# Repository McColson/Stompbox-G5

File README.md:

# Stompbox-G5
Guitar preamp stompbox

<br />Ce(tte) œuvre est mise à disposition selon les termes de la <a rel="license" href="http://creativecommons.org/licenses/by-nc-sa/4.0/">Licence Creative Commons Attribution - Pas d’Utilisation Commerciale - Partage dans les Mêmes Conditions 4.0 International</a>.

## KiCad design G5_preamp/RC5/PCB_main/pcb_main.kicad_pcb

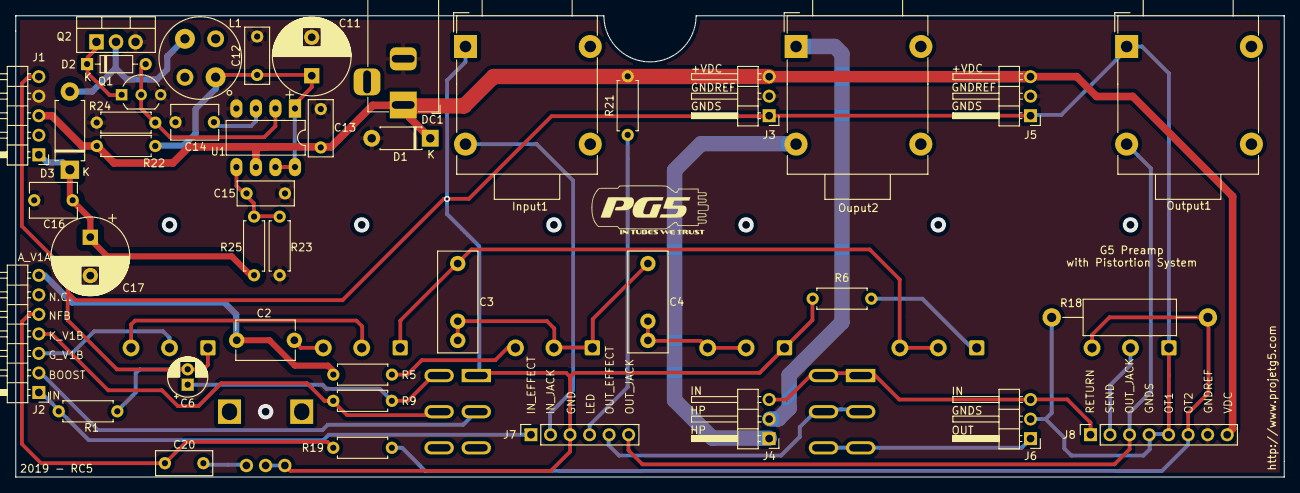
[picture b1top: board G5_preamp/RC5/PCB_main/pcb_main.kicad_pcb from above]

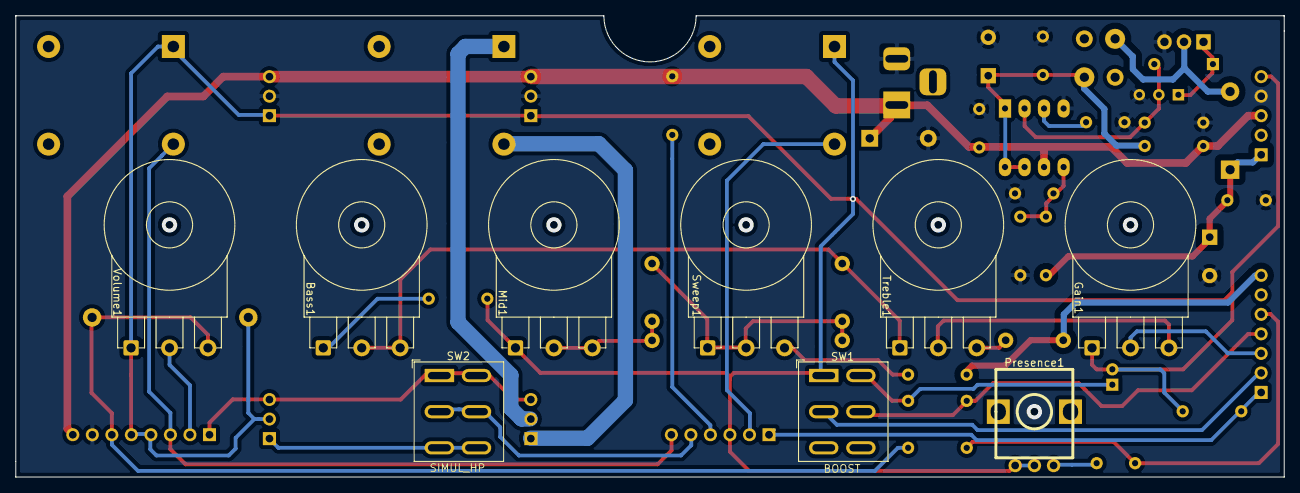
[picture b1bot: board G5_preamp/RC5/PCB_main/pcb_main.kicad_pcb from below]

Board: 2 copper layers, 165.0 x 60.0 mm, 52 parts (9 on the bottom side), 35 nets.

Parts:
Bass1: 250k log; Potentiometer_Alpha_RV16AF41_Single_Vertical
C2: 250pF; C_Disc_D7.5mm_W5.0mm_P7.50mm
C3: 100nF; C_Rect_L13.0mm_W5.0mm_P7.5mm_or_P10.00mm_FKS3_FKP3_MKS4
C4: 47nF; C_Rect_L13.0mm_W5.0mm_P7.5mm_or_P10.00mm_FKS3_FKP3_MKS4
C6: 22µF/25V; CP_Radial_D5.0mm_P2.00mm
C11: 470µ; CP_Radial_D10.0mm_P5.00mm
C12, C13, C15: 100nf; C_Rect_L7.2mm_W3.0mm_P5.00mm_FKS2_FKP2_MKS2_MKP2
C14: 470p; C_Disc_D6.0mm_W4.4mm_P5.00mm
C16: 10n/400V; C_Disc_D6.0mm_W4.4mm_P5.00mm
C17: 4.7µ/400V; CP_Radial_D10.0mm_P5.00mm
C20: 470nf; C_Rect_L7.2mm_W3.0mm_P5.00mm_FKS2_FKP2_MKS2_MKP2
D1: 1N4007; D_DO-41_SOD81_P7.62mm_Horizontal
D2: 1N4148; D_DO-35_SOD27_P7.62mm_Horizontal
D3: BYV26; D_DO-15_P10.16mm_Horizontal
DC1: Barrel_Jack; BarrelJack_Horizontal
Gain1: 1M log; Potentiometer_Alpha_RV16AF41_Single_Vertical
Input1: Input; Jack_6.35mm_Neutrik_NMJ4HCD2_Horizontal
J1: PSU_TUBE; PinHeader_1x05_P2.54mm_Horizontal
J2: PCB_TUBE; PinHeader_1x07_P2.54mm_Horizontal
J3: PSU_AMP; PinHeader_1x03_P2.54mm_Horizontal
J4: AMP; PinHeader_1x03_P2.54mm_Horizontal
J5: PSU_SIMCAB; PinHeader_1x03_P2.54mm_Horizontal
J6: SIMCAB; PinHeader_1x03_P2.54mm_Horizontal
J7: 3PDT; PinSocket_1x06_P2.54mm_Vertical
J8: PCB_OUTPUT; PinSocket_1x08_P2.54mm_Vertical
L1: 220µH/1.5A; L_Radial_D10.5mm_P5.00mm_MuRATA_1200RS
Mid1: 100k log; Potentiometer_Alpha_RV16AF41_Single_Vertical
Ouput2: HP; Jack_6.35mm_Neutrik_NMJ4HCD2_Horizontal
Output1: Output; Jack_6.35mm_Neutrik_NMJ4HCD2_Horizontal
Presence1: 50k lin; RV09AF-40-ALPHA-POT
Q1: MPS751; TO-92_Inline_Wide
Q2: IRF740; TO-220-3_Vertical
R1: 1M; R_Axial_DIN0207_L6.3mm_D2.5mm_P7.62mm_Horizontal
R5: 47k; R_Axial_DIN0207_L6.3mm_D2.5mm_P7.62mm_Horizontal
R6: 15k; R_Axial_DIN0207_L6.3mm_D2.5mm_P7.62mm_Horizontal
R9, R21: 100k; R_Axial_DIN0207_L6.3mm_D2.5mm_P7.62mm_Horizontal
R18: 68R/2W; R_Axial_DIN0414_L11.9mm_D4.5mm_P20.32mm_Horizontal
R19: 1.5k; R_Axial_DIN0207_L6.3mm_D2.5mm_P7.62mm_Horizontal
R22: 0.22R; R_Axial_DIN0207_L6.3mm_D2.5mm_P7.62mm_Horizontal
R23: 1.8k; R_Axial_DIN0207_L6.3mm_D2.5mm_P7.62mm_Horizontal
R24: 1k; R_Axial_DIN0207_L6.3mm_D2.5mm_P7.62mm_Horizontal
R25: 430k; R_Axial_DIN0207_L6.3mm_D2.5mm_P7.62mm_Horizontal
SW1: Boost; SW_CK_Lever_DPDT_72xx
SW2: SIMCAB; SW_CK_Lever_DPDT_72xx
Sweep1: 50k lin; Potentiometer_Alpha_RV16AF41_Single_Vertical
Treble1: 250k lin; Potentiometer_Alpha_RV16AF41_Single_Vertical
U1: MC34063AP; DIP-8_W7.62mm_LongPads
U2: PG5_Logo; PG5_Logo_15mm_SilkScreen
Volume1: 1k; Potentiometer_Alpha_RV16AF41_Single_Vertical

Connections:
/A_V1A: C2.2, J2.7, R5.1
/BOOST: J2.2, SW1.2
/G_V1B: Gain1.2, J2.3
/HP1: J4.1, Ouput2.T
/HP2: J4.2, Ouput2.S
/HT1: D3.2, L1.2, Q2.2
/HT2: C16.1, C17.1, D3.1, J1.1, R25.1
/IN_EFFECT: J2.1, J7.1, R1.1
/IN_JACK: Input1.T, J7.2
/K_V1B: J2.4, R9.1, SW1.5
/LED: J7.4, R21.1
/NFB: C20.2, J2.5, R19.1
/OT2: J8.6, R18.1, R19.2, Volume1.3
/OUT_EFFECT: J7.5, SW2.2, SW2.5
/OUT_JACK: J7.6, J8.3, Output1.T
/PEAK: C11.1, C12.1, L1.1, R22.2, U1.1, U1.7, U1.8
/RETURN: J4.3, J6.3, J8.1, SW2.1, SW2.4
/SEND: J8.2, Volume1.2
/SIMCAB_OUT: J6.1, SW2.3, SW2.6
/VDC: C13.1, D1.1, DC1.1, J1.3, J3.3, J5.3, J8.8, R21.2, R22.1, U1.6
GNDREF: C11.2, C12.2, C13.2, C14.2, C15.2, C16.2, C17.2, D1.2, DC1.2, J1.4, J3.2, J5.2, J8.7, Q1.3, Q2.3, R23.2, R24.2, U1.4
GNDS: C6.2, Gain1.1, Input1.S, J1.5, J3.1, J5.1, J6.2, J7.3, J8.4, J8.5, Mid1.1, Output1.S, Presence1.1, Presence1.2, R1.2, R6.2, R18.2, SW1.1, Volume1.1
unnamed: Bass1.1, R6.1
unnamed: Bass1.2, Bass1.3, C3.1, Treble1.1
unnamed: C2.1, Treble1.3
unnamed: C3.2, C4.1, Sweep1.1, Sweep1.2
unnamed: C4.2, Mid1.2, Mid1.3
unnamed: C6.1, R9.2, SW1.4
unnamed: C14.1, U1.3
unnamed: C15.1, R23.1, R25.2, U1.5
unnamed: C20.1, Presence1.3
unnamed: D2.1, Q1.1, Q2.1
unnamed: D2.2, Q1.2, R24.1, U1.2
unnamed: Gain1.3, Treble1.2
unnamed: R5.2, Sweep1.3

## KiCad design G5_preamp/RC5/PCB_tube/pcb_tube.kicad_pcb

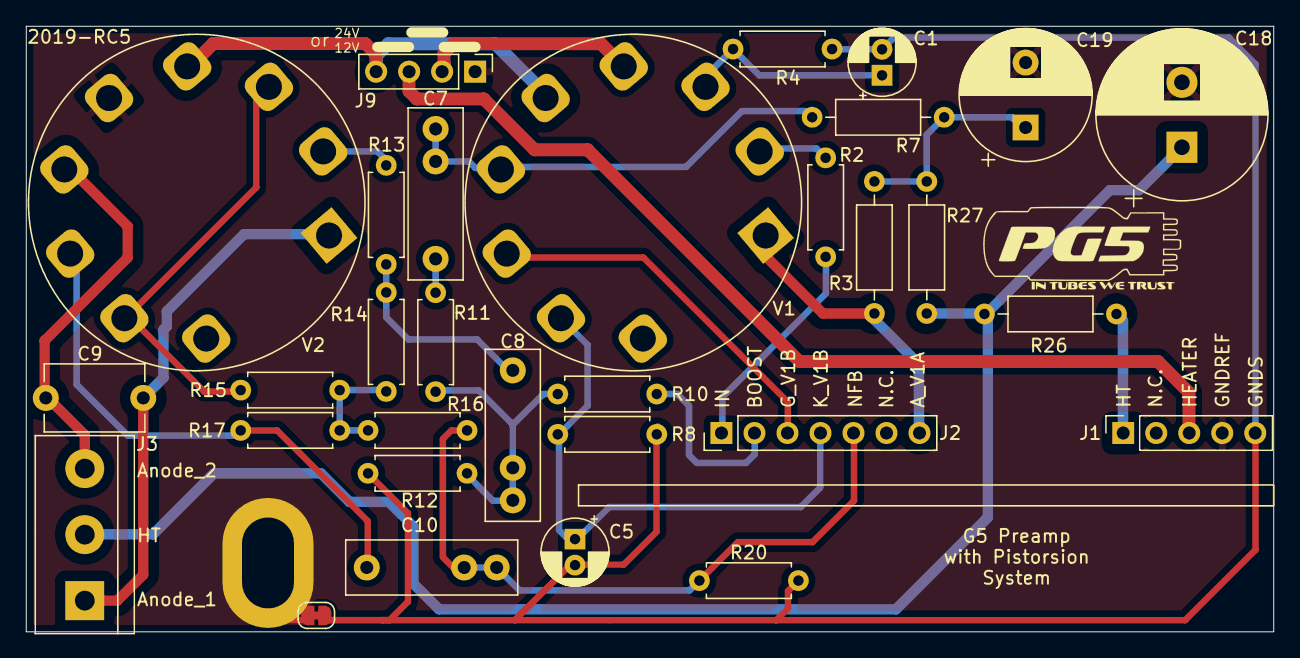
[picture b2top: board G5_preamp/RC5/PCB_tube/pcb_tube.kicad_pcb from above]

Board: 2 copper layers, 96.0 x 46.6 mm, 33 parts (0 on the bottom side), 26 nets.

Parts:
C1: 22µF/25v; CP_Radial_D5.0mm_P2.00mm
C5: 1µF/50v; CP_Radial_D5.0mm_P2.00mm
C7, C8: 22nF; C_Rect_L13.0mm_W4.0mm_P7.5mm_or_P10.00mm_MKS4
C9: 100pF; C_Disc_D7.5mm_W5.0mm_P7.50mm
C10: 10n; C_Rect_L13.0mm_W4.0mm_P7.5mm_or_P10.00mm_MKS4
C18: 22µF/400v; CP_Radial_D13.0mm_P5.00mm
C19: 10µF/400v; CP_Radial_D10.0mm_P5.00mm
H1: MountingHole_Pad; MountingHole_3.2mm_M3
J1: PSU_TUBE; PinSocket_1x05_P2.54mm_Vertical
J2: PCB_TUBE; PinHeader_1x07_P2.54mm_Vertical
J3: OT; TerminalBlock_bornier-3_P5.08mm
J9: Voltage_Heater; PinHeader_1x04_P2.54mm_Vertical
JP1: Jumper; SolderJumper-2_P1.3mm_Bridged_RoundedPad1.0x1.5mm
R2: 33k; R_Axial_DIN0207_L6.3mm_D2.5mm_P7.62mm_Horizontal
R3: 120k; R_Axial_DIN0207_L6.3mm_D2.5mm_P10.16mm_Horizontal
R4, R8: 1.8k; R_Axial_DIN0207_L6.3mm_D2.5mm_P7.62mm_Horizontal
R7: 100k; R_Axial_DIN0207_L6.3mm_D2.5mm_P10.16mm_Horizontal
R10: 100k; R_Axial_DIN0207_L6.3mm_D2.5mm_P7.62mm_Horizontal
R11, R12: 470k; R_Axial_DIN0207_L6.3mm_D2.5mm_P7.62mm_Horizontal
R13, R16: 10k; R_Axial_DIN0207_L6.3mm_D2.5mm_P7.62mm_Horizontal
R14, R17: 1M; R_Axial_DIN0207_L6.3mm_D2.5mm_P7.62mm_Horizontal
R15: 1k; R_Axial_DIN0207_L6.3mm_D2.5mm_P7.62mm_Horizontal
R20: 4.7k; R_Axial_DIN0207_L6.3mm_D2.5mm_P7.62mm_Horizontal
R26, R27: 1k; R_Axial_DIN0207_L6.3mm_D2.5mm_P10.16mm_Horizontal
U1: PG5_Logo; PG5_Logo_15mm_SilkScreen
V1, V2: ECC83; Valve_Noval-B9A_Belton-VT9-PT_Socket

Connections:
/A+: C18.1, J3.2, R26.2, R27.1
/A_V1A: J2.7, R3.2, V1.1
/A_V2A: C9.1, J3.3, V2.6
/A_V2B: C9.2, J3.1, V2.1
/BOOST: J2.2, R10.2
/G_V1B: J2.3, V1.7
/HEATER: J1.3, J9.3
/HEATER1: J9.2, V1.4
/HEATER2: J9.4, V1.5, V2.4
/HT2: J1.1, R26.1
/IN: J2.1, R2.2
/K_V1B: C5.1, J2.4, R8.1, V1.8
/NFB: C10.2, J2.5, R16.2, R20.1
GNDREF: C18.2, C19.2, H1.1, J1.4, J9.1, JP1.1, V2.5
GNDS: C1.2, C5.2, J1.5, JP1.2, R4.2, R8.2, R12.2, R20.2
unnamed: C1.1, R4.1, V1.3
unnamed: C7.1, R11.1
unnamed: C7.2, R7.2, V1.6
unnamed: C8.1, R13.2, R14.2
unnamed: C8.2, R10.1, R11.2, R12.1
unnamed: C10.1, R17.1, V2.7
unnamed: C19.1, R3.1, R7.1, R27.2
unnamed: R2.1, V1.2
unnamed: R13.1, V2.2
unnamed: R14.1, R15.2, R16.1, R17.2
unnamed: R15.1, V2.3, V2.8

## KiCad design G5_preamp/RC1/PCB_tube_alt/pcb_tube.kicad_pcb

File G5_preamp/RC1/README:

This version is obsolete, don't use it.

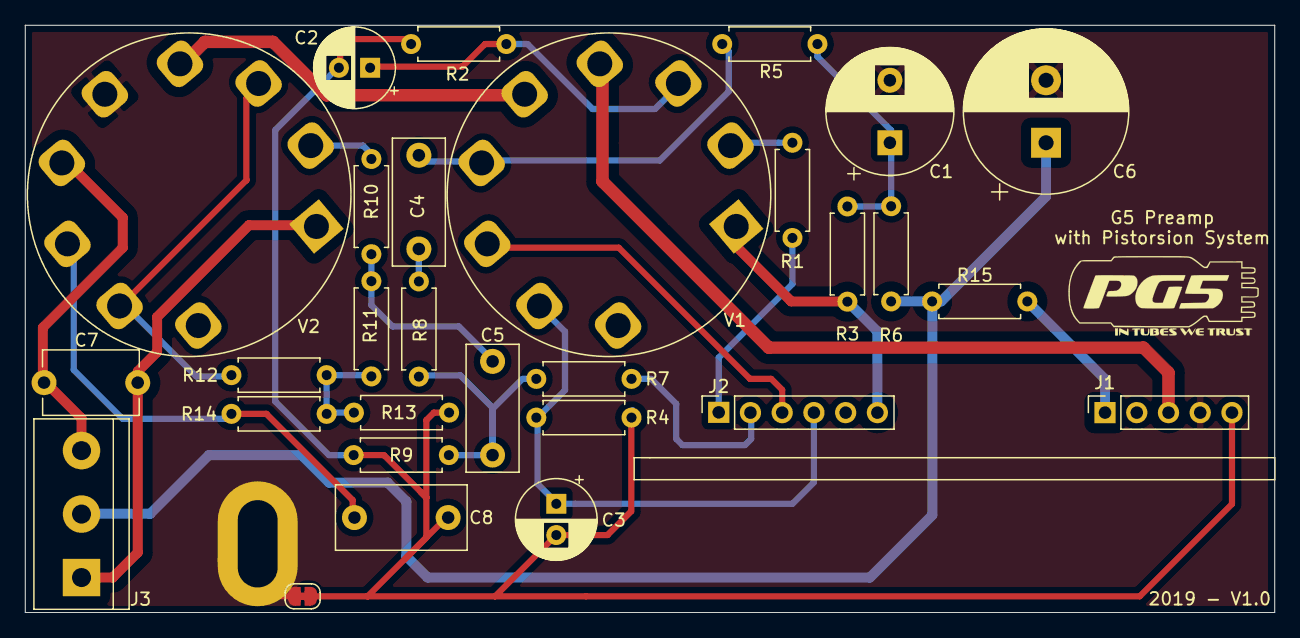
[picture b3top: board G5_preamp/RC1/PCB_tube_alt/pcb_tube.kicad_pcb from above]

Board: 2 copper layers, 100.0 x 47.0 mm, 29 parts (0 on the bottom side), 24 nets.

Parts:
C1: 10µF/350v; CP_Radial_D10.0mm_P5.00mm
C2: 22µF/25v; CP_Radial_D6.3mm_P2.50mm
C3: 1µF/25v; CP_Radial_D6.3mm_P2.50mm
C4, C5: 22nF; C_Rect_L10.0mm_W4.0mm_P7.50mm_MKS4
C6: 22µF/350v; CP_Radial_D13.0mm_P5.00mm
C7: 100pF; C_Disc_D7.5mm_W5.0mm_P7.50mm
C8: 100n; C_Rect_L10.3mm_W5.0mm_P7.50mm_MKS4
J1: PSU_TUBE; PinSocket_1x05_P2.54mm_Vertical
J2: PCB_TUBE; PinSocket_1x06_P2.54mm_Vertical
J3: OT; TerminalBlock_bornier-3_P5.08mm
JP1: Jumper; SolderJumper-2_P1.3mm_Bridged_RoundedPad1.0x1.5mm
R1: 33k; R_Axial_DIN0207_L6.3mm_D2.5mm_P7.62mm_Horizontal
R2, R4: 1.8k; R_Axial_DIN0207_L6.3mm_D2.5mm_P7.62mm_Horizontal
R3: 120k; R_Axial_DIN0207_L6.3mm_D2.5mm_P7.62mm_Horizontal
R5, R7: 100k; R_Axial_DIN0207_L6.3mm_D2.5mm_P7.62mm_Horizontal
R6, R12, R15: 1k; R_Axial_DIN0207_L6.3mm_D2.5mm_P7.62mm_Horizontal
R8, R9: 470k; R_Axial_DIN0207_L6.3mm_D2.5mm_P7.62mm_Horizontal
R10: 10k; R_Axial_DIN0207_L6.3mm_D2.5mm_P7.62mm_Horizontal
R11, R14: 1M; R_Axial_DIN0207_L6.3mm_D2.5mm_P7.62mm_Horizontal
R13: 47k; R_Axial_DIN0207_L6.3mm_D2.5mm_P7.62mm_Horizontal
V1, V2: ECC83; Valve_Noval-B9A_Belton-VT9-PT_Socket

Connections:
/24VDC: J1.3, V1.4
/A+: C6.1, J3.2, R6.1, R15.2
/A_V1A: J2.6, R3.2, V1.1
/A_V2A: C7.1, J3.3, V2.6
/A_V2B: C7.2, J3.1, V2.1
/BOOST: J2.2, R7.2
/G_V1B: J2.3, V1.7
/HEATER2: V1.5, V2.4
/HT2: J1.1, R15.1
/IN: J2.1, R1.2
/K_V1B: C3.1, J2.4, R4.1, V1.8
GNDREF: C1.2, C6.2, J1.4, JP1.1, V2.5
GNDS: C2.2, C3.2, C8.2, J1.5, JP1.2, R2.2, R4.2, R9.2, R13.2
unnamed: C1.1, R3.1, R5.1, R6.2
unnamed: C2.1, R2.1, V1.3
unnamed: C4.1, R8.1
unnamed: C4.2, R5.2, V1.6
unnamed: C5.1, R10.2, R11.2
unnamed: C5.2, R7.1, R8.2, R9.1
unnamed: C8.1, R14.1, V2.7
unnamed: R1.1, V1.2
unnamed: R10.1, V2.2
unnamed: R11.1, R12.2, R13.1, R14.2
unnamed: R12.1, V2.3, V2.8

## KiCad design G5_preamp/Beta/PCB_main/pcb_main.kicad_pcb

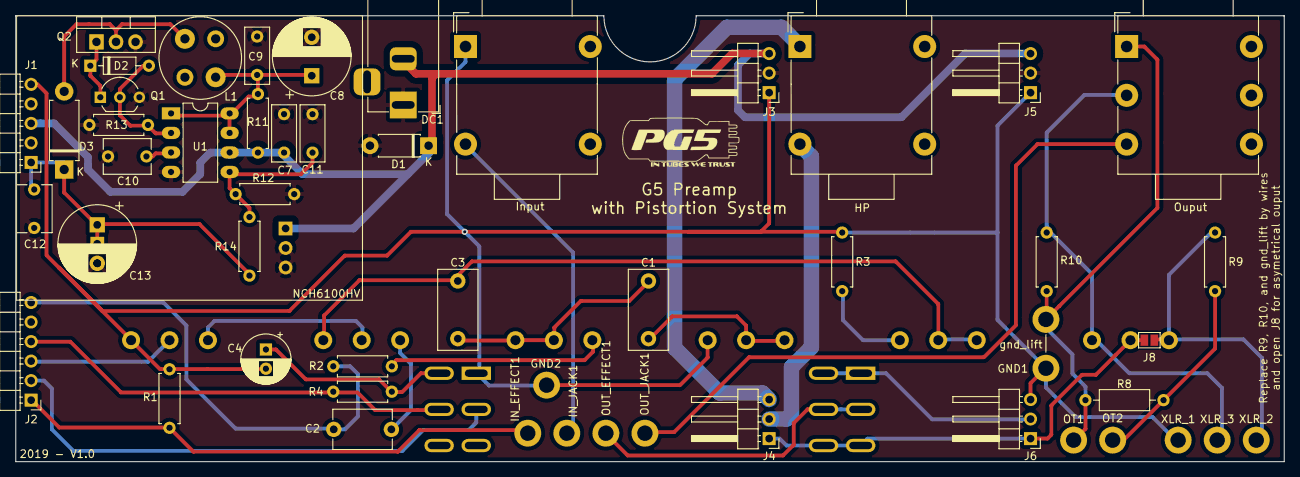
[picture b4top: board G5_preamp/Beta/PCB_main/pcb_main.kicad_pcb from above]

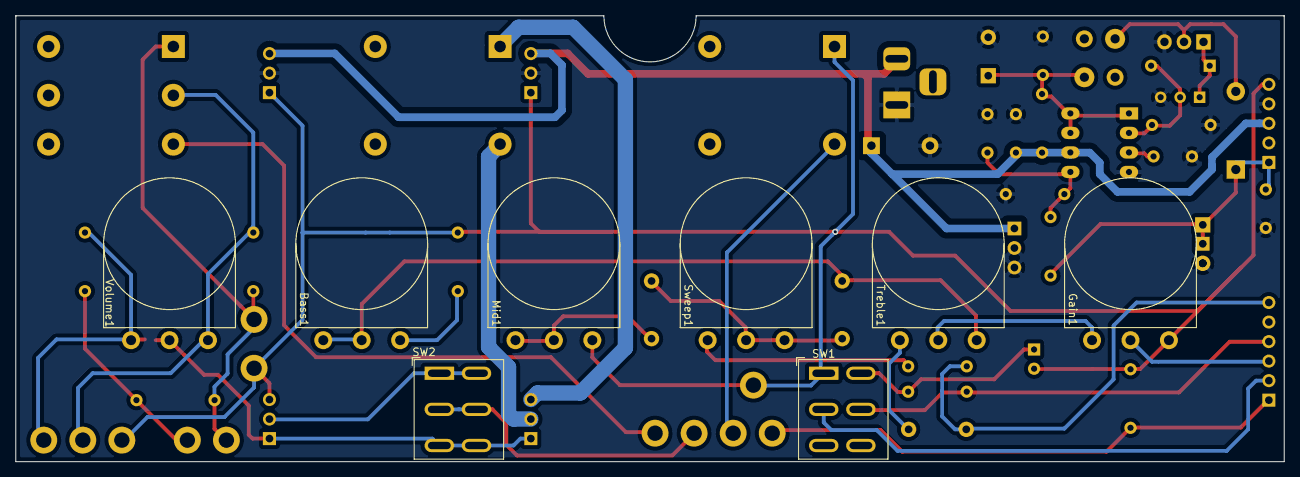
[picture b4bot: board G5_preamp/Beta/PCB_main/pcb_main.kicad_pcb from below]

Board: 2 copper layers, 165.0 x 58.0 mm, 60 parts (8 on the bottom side), 34 nets.

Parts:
Bass1: 250k log; Potentiometer_Omeg_PC16BU_Vertical
C1: 47nF; C_Rect_L10.3mm_W5.0mm_P7.50mm_MKS4
C2: 250pF; C_Disc_D7.5mm_W5.0mm_P7.50mm
C3: 100nF; C_Rect_L10.3mm_W5.0mm_P7.50mm_MKS4
C4: 22µF/35V; CP_Radial_D6.3mm_P2.50mm
C7, C9, C11: 100n; C_Rect_L7.2mm_W3.0mm_P5.00mm_FKS2_FKP2_MKS2_MKP2
C8: 470µ; CP_Radial_D10.0mm_P5.00mm
C10: 470p; C_Disc_D6.0mm_W4.4mm_P5.00mm
C12: 10n/400V; C_Disc_D6.0mm_W4.4mm_P5.00mm
C13: 4.7µ/350V; CP_Radial_D10.0mm_P5.00mm
D1: 1N4007; D_DO-41_SOD81_P7.62mm_Horizontal
D2: 1N4148; D_DO-35_SOD27_P7.62mm_Horizontal
D3: BYV26; D_DO-15_P10.16mm_Horizontal
DC1: Barrel_Jack; BarrelJack_Horizontal
GND1: GND; SolderWirePad_1x02_P7.62mm_Drill2mm
GND2: MASSE; SolderWirePad_1x01_Drill2mm
Gain1: 1M log; Potentiometer_Omeg_PC16BU_Vertical
HP: HP; Jack_6.35mm_Neutrik_NMJ4HCD2_Horizontal
IN_EFFECT1: IN_EFFECT; SolderWirePad_1x01_Drill2mm
IN_JACK1: IN_JACK; SolderWirePad_1x01_Drill2mm
Input: Input; Jack_6.35mm_Neutrik_NMJ4HCD2_Horizontal
J1: PSU_TUBE; PinHeader_1x05_P2.54mm_Horizontal
J2: PCB_TUBE; PinHeader_1x06_P2.54mm_Horizontal
J3: PSU_AMP; PinHeader_1x03_P2.54mm_Horizontal
J4: AMP; PinHeader_1x03_P2.54mm_Horizontal
J5: PSU_SIMCAB; PinHeader_1x03_P2.54mm_Horizontal
J6: SIMCAB; PinHeader_1x03_P2.54mm_Horizontal
J8: LEVEL 3-2; SolderJumper-2_P1.3mm_Open_Pad1.0x1.5mm
L1: 220µH/1.5A; L_Radial_D10.5mm_P5.00mm_MuRATA_1200RS
Mid1: 100k log; Potentiometer_Omeg_PC16BU_Vertical
NCH6100HV: NCH6100HV
OT1, OT2: 125A; SolderWirePad_1x01_Drill2mm
OUT_EFFECT1: 1; SolderWirePad_1x01_Drill2mm
OUT_JACK1: 1; SolderWirePad_1x01_Drill2mm
Ouput: Out; Jack_3.5mm_Neutrik_NMJ6HCD2_Horizontal
Q1: MPS751; TO-92_Inline_Wide
Q2: IRF740; TO-220-3_Vertical
R1: 1M; R_Axial_DIN0207_L6.3mm_D2.5mm_P7.62mm_Horizontal
R2: 47k; R_Axial_DIN0207_L6.3mm_D2.5mm_P7.62mm_Horizontal
R3: 15k; R_Axial_DIN0207_L6.3mm_D2.5mm_P7.62mm_Horizontal
R4: 100k; R_Axial_DIN0207_L6.3mm_D2.5mm_P7.62mm_Horizontal
R8: 100R/2W; R_Axial_DIN0207_L6.3mm_D2.5mm_P10.16mm_Horizontal
R9, R10: 330R; R_Axial_DIN0207_L6.3mm_D2.5mm_P7.62mm_Horizontal
R11: 0.22R; R_Axial_DIN0207_L6.3mm_D2.5mm_P7.62mm_Horizontal
R12: 1.8k; R_Axial_DIN0207_L6.3mm_D2.5mm_P7.62mm_Horizontal
R13: 1k; R_Axial_DIN0207_L6.3mm_D2.5mm_P7.62mm_Horizontal
R14: 430k; R_Axial_DIN0207_L6.3mm_D2.5mm_P7.62mm_Horizontal
SW1: Boost; SW_CK_Lever_DPDT_72xx
SW2: SIMCAB; SW_CK_Lever_DPDT_72xx
Sweep1: 50k lin; Potentiometer_Omeg_PC16BU_Vertical
Treble1: 250k lin; Potentiometer_Omeg_PC16BU_Vertical
U1: MC34063AP; DIP-8_W7.62mm_LongPads
Volume1: 1k; Potentiometer_Omeg_PC16BU_Vertical
XLR_1: 1; SolderWirePad_1x01_Drill2mm
XLR_2: 2; SolderWirePad_1x01_Drill2mm
XLR_3: 3; SolderWirePad_1x01_Drill2mm

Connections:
+24V: C7.1, D1.1, DC1.2, J1.3, J3.3, J5.3, NCH6100HV.1, R11.1, U1.6
/A_V1A: C2.2, J2.6, R2.1
/BOOST: J2.2, SW1.2
/G_V1B: Gain1.2, J2.3
/HP1: HP.T, J4.2
/HP2: HP.S, J4.3
/HT1: D3.2, L1.2, Q2.2
/HT2: C12.1, C13.1, D3.1, J1.1, NCH6100HV.4, R14.1
/IN_EFFECT: IN_EFFECT1.1, J2.1, R1.1
/K_V1B: J2.4, R4.1, SW1.5
/LINE_OUT: J4.1, J6.1, J8.2, SW2.3, SW2.6, Volume1.2
/PEAK: C8.1, C9.1, L1.1, R11.2, U1.1, U1.7, U1.8
/SIMCAB_OUT: J6.2, SW2.1, SW2.4
GNDREF: C7.2, C8.2, C9.2, C10.2, C11.2, C12.2, C13.2, D1.2, DC1.1, J1.4, J3.2, J5.2, NCH6100HV.2, NCH6100HV.3, NCH6100HV.5, Q1.3, Q2.3, R12.2, R13.2, U1.4
GNDS: C4.2, GND1.2, GND2.1, Gain1.1, Input.S, J1.5, J3.1, J5.1, J6.3, Mid1.1, R1.2, R3.2, SW1.1, XLR_1.1
unnamed: Bass1.1, R3.1
unnamed: Bass1.2, Bass1.3, C3.1, Treble1.1
unnamed: C1.1, C3.2, Sweep1.1, Sweep1.2
unnamed: C1.2, Mid1.2, Mid1.3
unnamed: C2.1, Treble1.3
unnamed: C4.1, R4.2, SW1.4
unnamed: C10.1, U1.3
unnamed: C11.1, R12.1, R14.2, U1.5
unnamed: D2.1, Q1.1, Q2.1
unnamed: D2.2, Q1.2, R13.1, U1.2
unnamed: GND1.1, OT1.1, Ouput.S, R8.2, R10.2
unnamed: Gain1.3, Treble1.2
unnamed: IN_JACK1.1, Input.T
unnamed: J8.1, R9.1, Volume1.3, XLR_2.1
unnamed: OT2.1, R8.1, R9.2
unnamed: OUT_EFFECT1.1, SW2.2, SW2.5
unnamed: OUT_JACK1.1, Ouput.T
unnamed: Ouput.R, R10.1, Volume1.1, XLR_3.1
unnamed: R2.2, Sweep1.3

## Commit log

2019-02-27 Add licence CC
2019-04-05 Version1
2019-04-05 Rename
    rename to G5_preamp
2019-04-19 DC-DC move
    DC-DC Converter move from PCB_tube to PCB_main
2019-04-19 Gerber export
    Last MAJ with GERBER
2019-04-21 RC1
    Release Candidate 1
2019-04-22 Validation RC1
    Commande PCB
2019-04-23 Licence CC
    Information licence CC on schematic and pcb files
2019-04-25 RC2
    Release Candidate 2
2019-04-26 BOM adjustement
2019-04-28 DC jack Polarity change
    DC Jack polarity change and some capacitor footprint mod
2019-04-29 Reverse SimulHP switch
2019-05-02 3D setting
2019-05-02 Update G5_preamp.pdf
    New Schematic annotation
2019-05-05 GND lift arrangement
    GND lift arrangement
2019-05-07 Remove NCH6100HV
2019-05-07 Pad fixation pcb_tube
2019-05-07 mod pcb_tube
2019-05-07 Update fp-info-cache
2019-05-08 Schematic G5_preamp
2019-05-09 RC3 Update
2019-05-09 RC3 update
    Cathode Cap change 3d models and place (pcb-main)
2019-05-10 Screenshots
2019-05-12 RC3 multivoltage
2019-05-12 RC4
    Add presence potentiometer and NFB
2019-05-24 BOM adjust
2019-05-24 update pcb_main tracks
2019-05-24 Cosmetic_update_pcb
    R6 move
2019-07-01 Create préampli_G5.pdf
    RC6
2019-07-01 RC6
    RC6

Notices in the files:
G5_preamp/RC1/PCB_tube_alt/pcb_tube.kicad_pcb:
Licence under Creative Commons BY-NC-SA 4.0
